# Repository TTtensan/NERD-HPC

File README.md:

# [NERD-HPC](https://github.com/TTtensan/NERD-HPC)

## アップデート方法
1. 本体とPCをUSBで接続する。
2. BOOTを押しながらPowerをONにする。もしくはPowerをONにした後にBOOTを押しながらRESETボタンを押す。
3. パソコンにRPI-RP2として認識されるのでsoftware/build/src/NERD_HPC.uf2をドラッグ&ドロップする。

## ファームウェアのビルド方法
どちらの方法でも、ビルド成果物は`software/build/src/NERD_HPC.uf2`に出力されます。

### コマンドラインでビルドする場合
```
(Ubuntu Desktop 24.04.1 LTS)
sudo apt install cmake python3 build-essential gcc-arm-none-eabi libnewlib-arm-none-eabi libstdc++-arm-none-eabi-newlib
```
```
git clone --recursive https://github.com/TTtensan/NERD-HPC.git
cd NERD-HPC/software
cmake -B build
cd build
make
```
この方法では、リポジトリに同梱されている`software/libraries/pico-sdk`(サブモジュール)を使ってビルドします。`--recursive`を忘れずに。

### VS Codeでビルドする場合
[Raspberry Pi Pico拡張機能](https://marketplace.visualstudio.com/items?itemName=raspberry-pi.raspberry-pi-pico)を使います。

1. リポジトリをクローンし、`software`フォルダをVS Codeで開く。
2. 推奨拡張機能のインストールを促されるので、インストールする(`.vscode/extensions.json`に定義しています)。
3. Pico拡張機能が必要なツールチェーンを`~/.pico-sdk`以下に自動でダウンロードします。使用するバージョンは`software/CMakeLists.txt`の先頭で指定しています(Pico SDK 2.2.0 / GCC 14_2_Rel1 / picotool 2.2.0-a4)。
4. サイドバーのPicoアイコンから`Compile Project`を実行する。

`.vscode`以下の設定はリポジトリで共有しています。パスはすべて`${userHome}`などの変数で書いてあるため、Windows・macOS・Linuxのいずれでもそのまま動作します。

なお、この方法ではコマンドラインの場合と違い、同梱のサブモジュールではなく`~/.pico-sdk`にダウンロードされたSDKが使われます。

## その他リンク
- 本家豊四季タイニーBASIC(Arduino版)。素晴らしいプログラムをオープンソースライセンスで公開いただいていること、大変感謝しています。製作者様に本オープンソースプロジェクトについて連絡済みです。GPLのバージョンはGPLv3とのこと。<br>[ttbasic\_arduino](https://github.com/vintagechips/ttbasic_arduino)

- CHR、2進数、16進数の処理はこちらを参考にしました。大変参考になりました。<br>[ttbasic\_arduino\_stm32](https://github.com/Tamakichi/ttbasic_arduino_stm32)

- フォントデータ。こちらをベースに一部変更しています。これによって少ないデータでフォントデータを実装することができました。ありがとうございます。<br>[ＡＱＭ１２４８Ａ グラフィックＬＣＤ (for Arduino)](https://hatakekara.com/aqm1248a/)

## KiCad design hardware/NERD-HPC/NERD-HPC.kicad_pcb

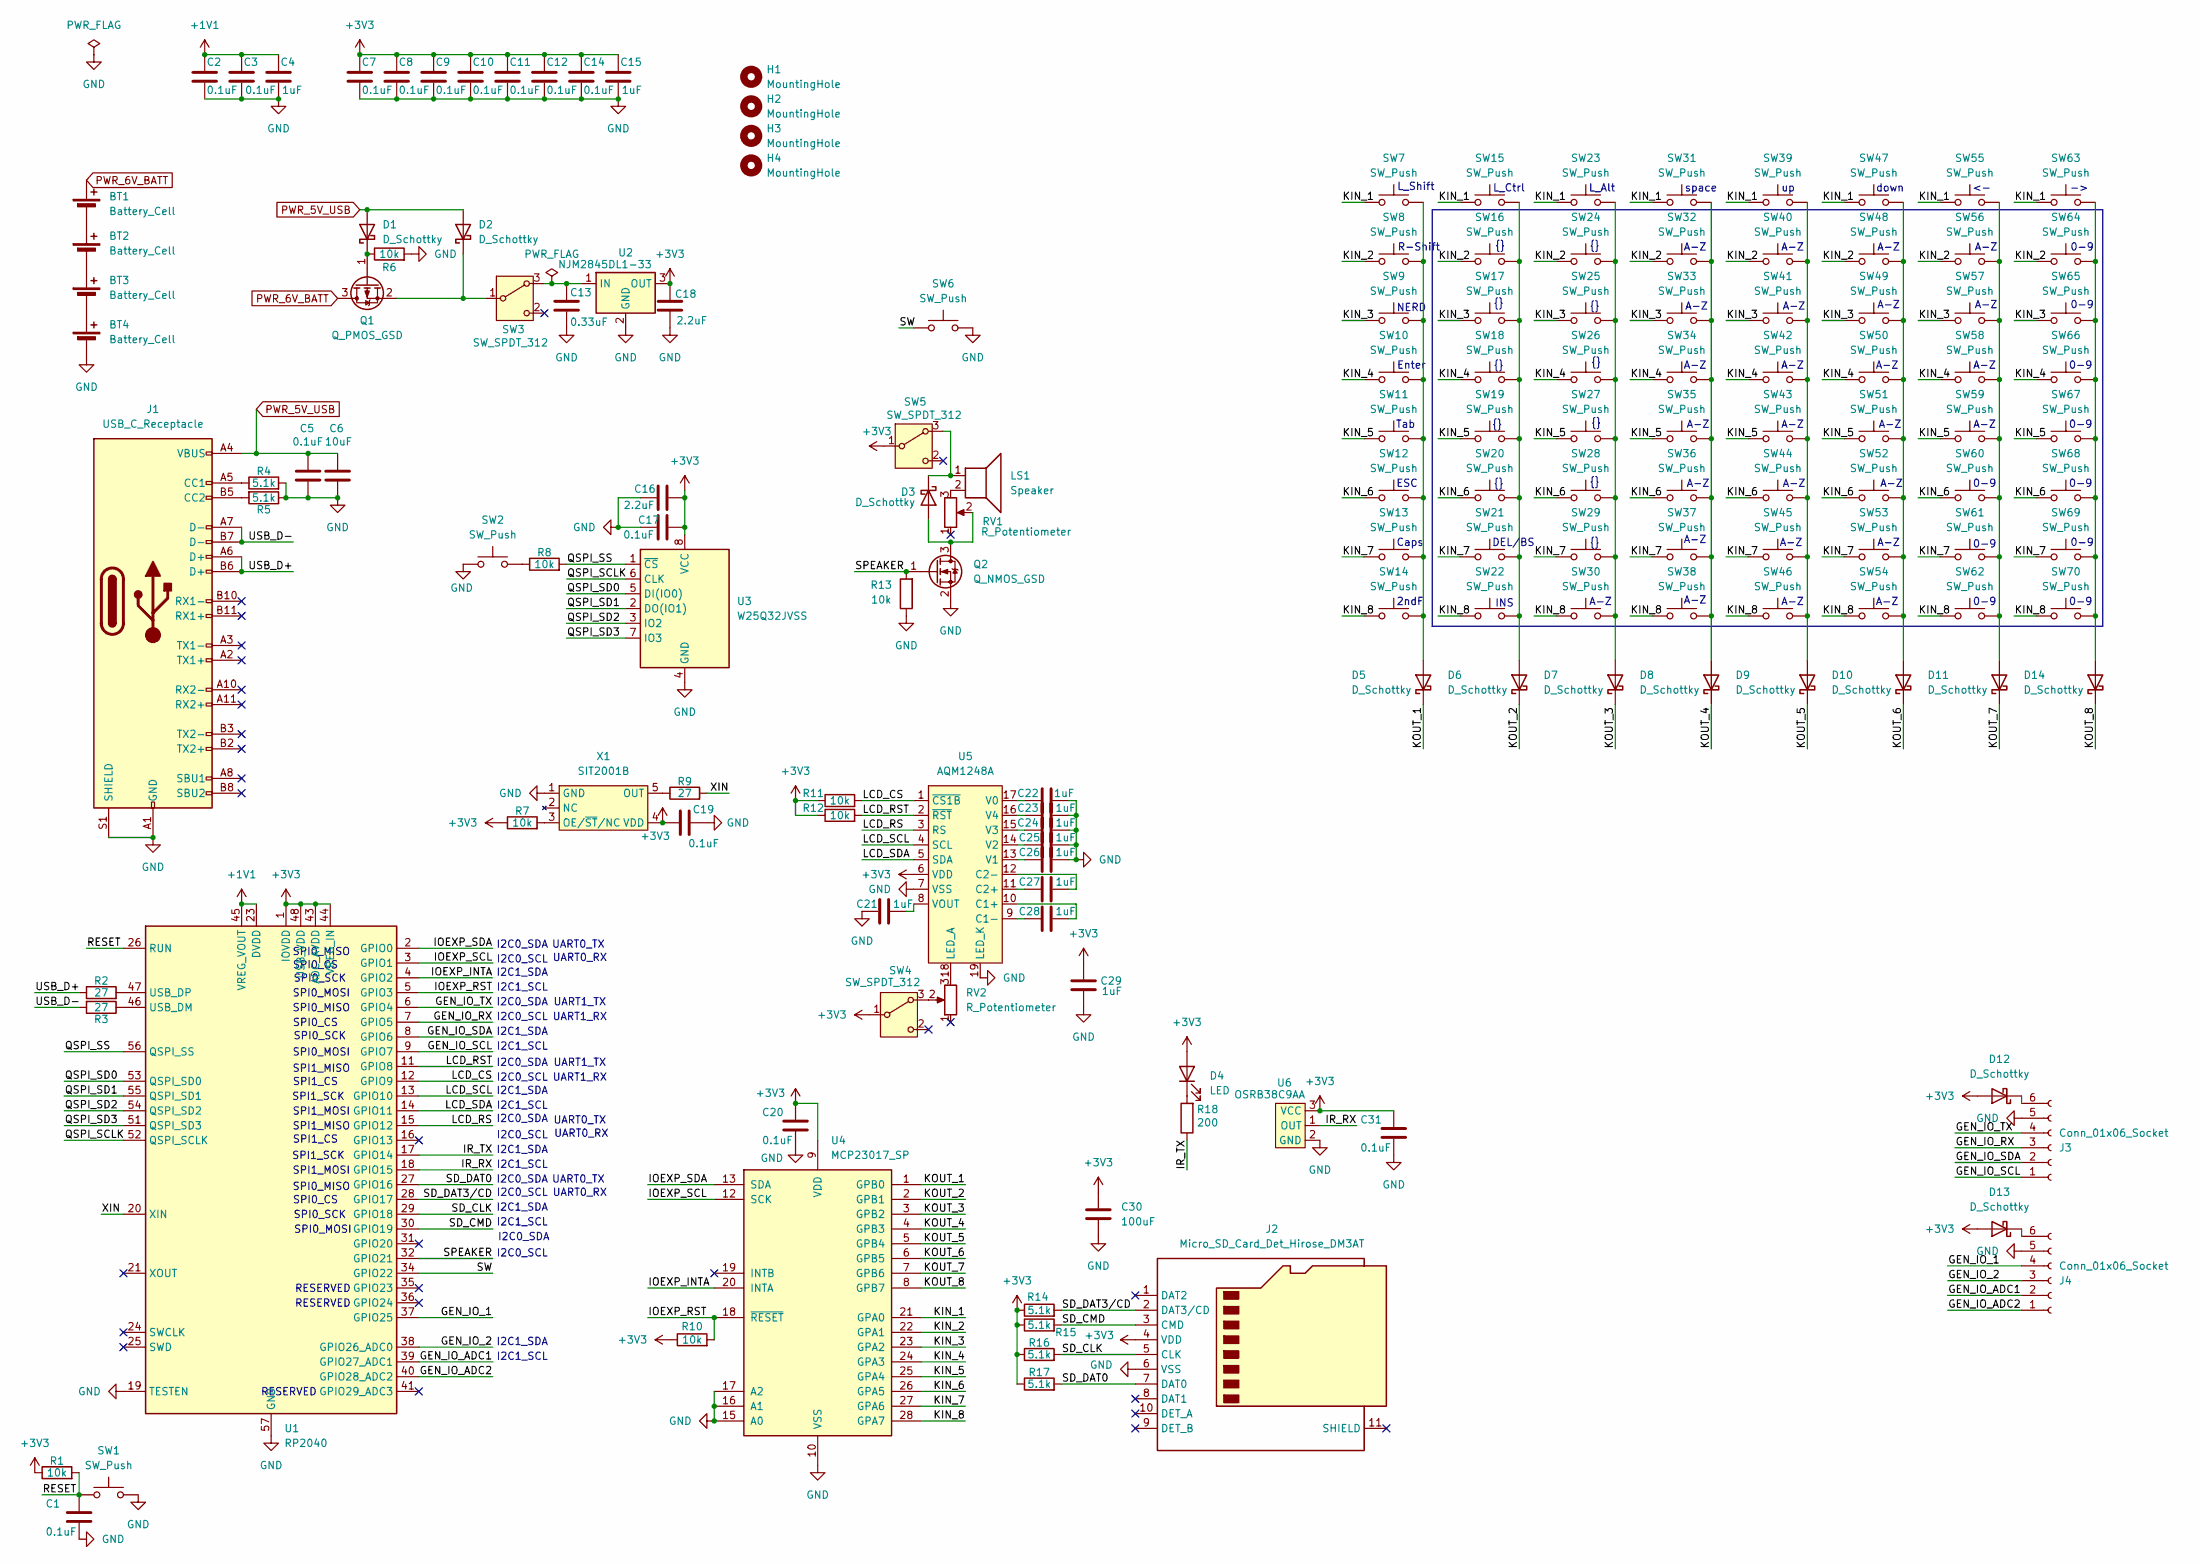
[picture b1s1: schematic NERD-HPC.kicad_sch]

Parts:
BT1, BT2, BT3, BT4: Battery_Cell; BatteryHolder_Keystone_2466_1xAAA
C1, C2, C3, C5, C7, C8, C9, C10, C11, C12, C14, C17, C19, C20, C31: 0.1uF; C_0603_1608Metric
C4, C15, C21, C22, C23, C24, C25, C26, C27, C28, C29: 1uF; C_0603_1608Metric
C6: 10uF; C_0603_1608Metric
C13: 0.33uF; C_0603_1608Metric
C16, C18: 2.2uF; C_0603_1608Metric
C30: 100uF; C_1206_3216Metric
D1, D2, D3, D5, D6, D7, D8, D9, D10, D11, D12, D13, D14: D_Schottky; CUS01
D4: LED; LED_D3.0mm
H1, H2, H3, H4: MountingHole; MountingHole_3.2mm_M3
J1: USB_C_Receptacle; USB_C_Receptacle_XKB_U262-16XN-4BVC11
J2: Micro_SD_Card_Det_Hirose_DM3AT; microSD_HC_Hirose_DM3AT-SF-PEJM5
J3, J4: Conn_01x06_Socket; PinSocket_1x06_P2.54mm_Vertical
LS1: Speaker; UM1515IA085008
Q1: Q_PMOS_GSD; SOT-23
Q2: Q_NMOS_GSD; SOT-23
R1, R6, R7, R8, R10, R11, R12, R13: 10k; R_0603_1608Metric
R2, R3, R9: 27; R_0603_1608Metric
R4, R5, R14, R15, R16, R17: 5.1k; R_0603_1608Metric
R18: 200; R_0603_1608Metric
RV1, RV2: R_Potentiometer; 3386K-EY5-101TR
SW1, SW2, SW6, SW7, SW8, SW9, SW10, SW11, SW12, SW13, SW14, SW15, SW16, SW17, SW18, SW19, SW20, SW21, SW22, SW23, SW24, SW25, SW26, SW27, SW28, SW29, SW30, SW31, SW32, SW33, SW34, SW35, SW36, SW37, SW38, SW39, SW40, SW41, SW42, SW43, SW44, SW45, SW46, SW47, SW48, SW49, SW50, SW51, SW52, SW53, SW54, SW55, SW56, SW57, SW58, SW59, SW60, SW61, SW62, SW63, SW64, SW65, SW66, SW67, SW68, SW69, SW70: SW_Push; SW_PUSH_6mm
SW3, SW4, SW5: SW_SPDT_312; SS-12D00-G5
U1: RP2040; QFN-56-1EP_7x7mm_P0.4mm_EP3.2x3.2mm
U2: NJM2845DL1-33; TO-252-3_TabPin2
U3: W25Q32JVSS; Winbond_USON-8-1EP_3x2mm_P0.5mm_EP0.2x1.6mm
U4: MCP23017_SP; DIP-28_W7.62mm
U5: AQM1248A
U6: OSRB38C9AA
X1: SIT2001B; SOT-23-5

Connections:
+1V1: C2.1, C3.1, C4.1, U1.23 (DVDD), U1.45 (VREG_VOUT), U1.50 (DVDD)
+3V3: C7.1, C8.1, C9.1, C10.1, C11.1, C12.1, C14.1, C15.1, C16.2, C17.1, C18.1, C19.2, C20.1, C29.1, C30.1, C31.1, D4.2 (A), D12.2 (A), D13.2 (A), J2.4 (VDD), R1.1, R7.1, R10.1, R11.1, R12.1, R14.1, R15.1, R16.1, R17.1, SW4.1 (B), SW5.1 (B), U1.1 (IOVDD), U1.10 (IOVDD), U1.22 (IOVDD), U1.33 (IOVDD), U1.42 (IOVDD), U1.43 (ADC_AVDD), U1.44 (VREG_IN), U1.48 (USB_VDD), U1.49 (IOVDD), U2.3 (OUT), U3.8 (VCC), U4.9 (VDD), U5.6 (VDD), U6.3 (VCC), X1.4 (VDD)
/GEN_IO_1: J4.4, U1.37 (GPIO25)
/GEN_IO_2: J4.3, U1.38 (GPIO26_ADC0)
/GEN_IO_ADC1: J4.2, U1.39 (GPIO27_ADC1)
/GEN_IO_ADC2: J4.1, U1.40 (GPIO28_ADC2)
/GEN_IO_RX: J3.3, U1.7 (GPIO5)
/GEN_IO_SCL: J3.1, U1.9 (GPIO7)
/GEN_IO_SDA: J3.2, U1.8 (GPIO6)
/GEN_IO_TX: J3.4, U1.6 (GPIO4)
/IOEXP_INTA: U1.4 (GPIO2), U4.20 (INTA)
/IOEXP_RST: R10.2, U1.5 (GPIO3), U4.18 (~RESET)
/IOEXP_SCL: U1.3 (GPIO1), U4.12 (SCK)
/IOEXP_SDA: U1.2 (GPIO0), U4.13 (SDA)
/IR_RX: U1.18 (GPIO15), U6.1 (OUT)
/IR_TX: R18.1, U1.17 (GPIO14)
/KIN_1: SW7.1, SW15.1, SW23.1, SW31.1, SW39.1, SW47.1, SW55.1, SW63.1, U4.21 (GPA0)
/KIN_2: SW8.1, SW16.1, SW24.1, SW32.1, SW40.1, SW48.1, SW56.1, SW64.1, U4.22 (GPA1)
/KIN_3: SW9.1, SW17.1, SW25.1, SW33.1, SW41.1, SW49.1, SW57.1, SW65.1, U4.23 (GPA2)
/KIN_4: SW10.1, SW18.1, SW26.1, SW34.1, SW42.1, SW50.1, SW58.1, SW66.1, U4.24 (GPA3)
/KIN_5: SW11.1, SW19.1, SW27.1, SW35.1, SW43.1, SW51.1, SW59.1, SW67.1, U4.25 (GPA4)
/KIN_6: SW12.1, SW20.1, SW28.1, SW36.1, SW44.1, SW52.1, SW60.1, SW68.1, U4.26 (GPA5)
/KIN_7: SW13.1, SW21.1, SW29.1, SW37.1, SW45.1, SW53.1, SW61.1, SW69.1, U4.27 (GPA6)
/KIN_8: SW14.1, SW22.1, SW30.1, SW38.1, SW46.1, SW54.1, SW62.1, SW70.1, U4.28 (GPA7)
/KOUT_1: D5.1 (K), U4.1 (GPB0)
/KOUT_2: D6.1 (K), U4.2 (GPB1)
/KOUT_3: D7.1 (K), U4.3 (GPB2)
/KOUT_4: D8.1 (K), U4.4 (GPB3)
/KOUT_5: D9.1 (K), U4.5 (GPB4)
/KOUT_6: D10.1 (K), U4.6 (GPB5)
/KOUT_7: D11.1 (K), U4.7 (GPB6)
/KOUT_8: D14.1 (K), U4.8 (GPB7)
/LCD_CS: R11.2, U1.12 (GPIO9), U5.1 (~CS1B)
/LCD_RS: U1.15 (GPIO12), U5.3 (RS)
/LCD_RST: R12.2, U1.11 (GPIO8), U5.2 (~RST)
/LCD_SCL: U1.13 (GPIO10), U5.4 (SCL)
/LCD_SDA: U1.14 (GPIO11), U5.5 (SDA)
/QSPI_SCLK: U1.52 (QSPI_SCLK), U3.6 (CLK)
/QSPI_SD0: U1.53 (QSPI_SD0), U3.5 (DI(IO0))
/QSPI_SD1: U1.55 (QSPI_SD1), U3.2 (DO(IO1))
/QSPI_SD2: U1.54 (QSPI_SD2), U3.3 (IO2)
/QSPI_SD3: U1.51 (QSPI_SD3), U3.7 (IO3)
/QSPI_SS: R8.2, U1.56 (QSPI_SS), U3.1 (~CS)
/RESET: C1.1, R1.2, SW1.1, U1.26 (RUN)
/SD_CLK: J2.5 (CLK), R16.2, U1.29 (GPIO18)
/SD_CMD: J2.3 (CMD), R15.2, U1.30 (GPIO19)
/SD_DAT0: J2.7 (DAT0), R17.2, U1.27 (GPIO16)
/SD_DAT3/CD: J2.2 (DAT3/CD), R14.2, U1.28 (GPIO17)
/SPEAKER: Q2.1 (G), R13.2, U1.32 (GPIO21)
/SW: SW6.1, U1.34 (GPIO22)
/USB_D+: J1.A6 (D+), J1.B6 (D+), R2.1
/USB_D-: J1.A7 (D-), J1.B7 (D-), R3.2
/XIN: R9.2, U1.20 (XIN)
GND: BT4.2 (-), C1.2, C2.2, C3.2, C4.2, C5.2, C6.2, C7.2, C8.2, C9.2, C10.2, C11.2, C12.2, C13.2, C14.2, C15.2, C16.1, C17.2, C18.2, C19.1, C20.2, C21.1, C22.2, C23.2, C24.2, C25.2, C26.2, C29.2, C30.2, C31.2, J1.A1 (GND), J1.A12 (GND), J1.B1 (GND), J1.B12 (GND), J1.S1 (SHIELD), J2.6 (VSS), J3.5, J4.5, Q2.2 (S), R4.2, R5.1, R6.2, R13.1, SW1.2, SW2.1, SW6.2, U1.19 (TESTEN), U1.57 (GND), U2.2 (GND), U3.4 (GND), U4.10 (VSS), U4.15 (A0), U4.16 (A1), U4.17 (A2), U5.7 (VSS), U5.19 (LED_K), U6.2 (GND), X1.1 (GND)
unnamed: BT1.2 (-), BT2.1 (+)
unnamed: BT2.2 (-), BT3.1 (+)
unnamed: BT3.2 (-), BT4.1 (+)
unnamed: D1.1 (K), Q1.1 (G), R6.1
unnamed: D2.1 (K), Q1.2 (S), SW3.1 (B)
unnamed: D3.2 (A), Q2.3 (D), RV1.2
unnamed: D3.1 (K), LS1.1, SW5.3 (A)
unnamed: D4.1 (K), R18.2
unnamed: D5.2 (A), SW7.2, SW8.2, SW9.2, SW10.2, SW11.2, SW12.2, SW13.2, SW14.2
unnamed: D6.2 (A), SW15.2, SW16.2, SW17.2, SW18.2, SW19.2, SW20.2, SW21.2, SW22.2
unnamed: D7.2 (A), SW23.2, SW24.2, SW25.2, SW26.2, SW27.2, SW28.2, SW29.2, SW30.2
unnamed: D8.2 (A), SW31.2, SW32.2, SW33.2, SW34.2, SW35.2, SW36.2, SW37.2, SW38.2
unnamed: D9.2 (A), SW39.2, SW40.2, SW41.2, SW42.2, SW43.2, SW44.2, SW45.2, SW46.2
unnamed: D10.2 (A), SW47.2, SW48.2, SW49.2, SW50.2, SW51.2, SW52.2, SW53.2, SW54.2
unnamed: D11.2 (A), SW55.2, SW56.2, SW57.2, SW58.2, SW59.2, SW60.2, SW61.2, SW62.2
unnamed: D12.1 (K), J3.6
unnamed: D13.1 (K), J4.6
unnamed: D14.2 (A), SW63.2, SW64.2, SW65.2, SW66.2, SW67.2, SW68.2, SW69.2, SW70.2
unnamed: J1.A5 (CC1), R4.1
unnamed: J1.B5 (CC2), R5.2
unnamed: LS1.2, RV1.3
unnamed: R8.1, SW2.2
unnamed: C13.1, SW3.3 (A), U2.1 (IN)
unnamed: RV2.2, SW4.3 (A)
unnamed: R3.1, U1.46 (USB_DM)
unnamed: R2.2, U1.47 (USB_DP)
unnamed: C28.2, U5.10 (C1+)
unnamed: C28.1, U5.9 (C1-)
unnamed: C27.1, U5.11 (C2+)
unnamed: C27.2, U5.12 (C2-)
unnamed: RV2.3, U5.18 (LED_A)
unnamed: C22.1, U5.17 (V0)
unnamed: C26.1, U5.13 (V1)
unnamed: C25.1, U5.14 (V2)
unnamed: C24.1, U5.15 (V3)
unnamed: C23.1, U5.16 (V4)
unnamed: C21.2, U5.8 (VOUT)
unnamed: R7.2, X1.3 (OE/~ST/NC)
unnamed: R9.1, X1.5 (OUT)
PWR_5V_USB: C5.1, C6.1, D1.2 (A), D2.2 (A), J1.A4 (VBUS), J1.A9 (VBUS), J1.B4 (VBUS), J1.B9 (VBUS)
PWR_6V_BATT: BT1.1 (+), Q1.3 (D)

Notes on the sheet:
A-Z
I2C1_SDA
I2C0_SDA
ESC
SPI1_MOSI
0-9
UART0_RX
2ndF
Tab
SPI0_SCK
I2C1_SCL
I2C0_SCL
RESERVED
DEL/BS
SPI0_CS
Caps
SPI0_MISO
SPI1_CS
UART1_RX
Enter
SPI1_SCK
R-Shift
down
UART1_TX
SPI0_MOSI
SPI1_MISO
L_Ctrl
UART0_TX
NERD
L_Alt
L_Shift
INS
space

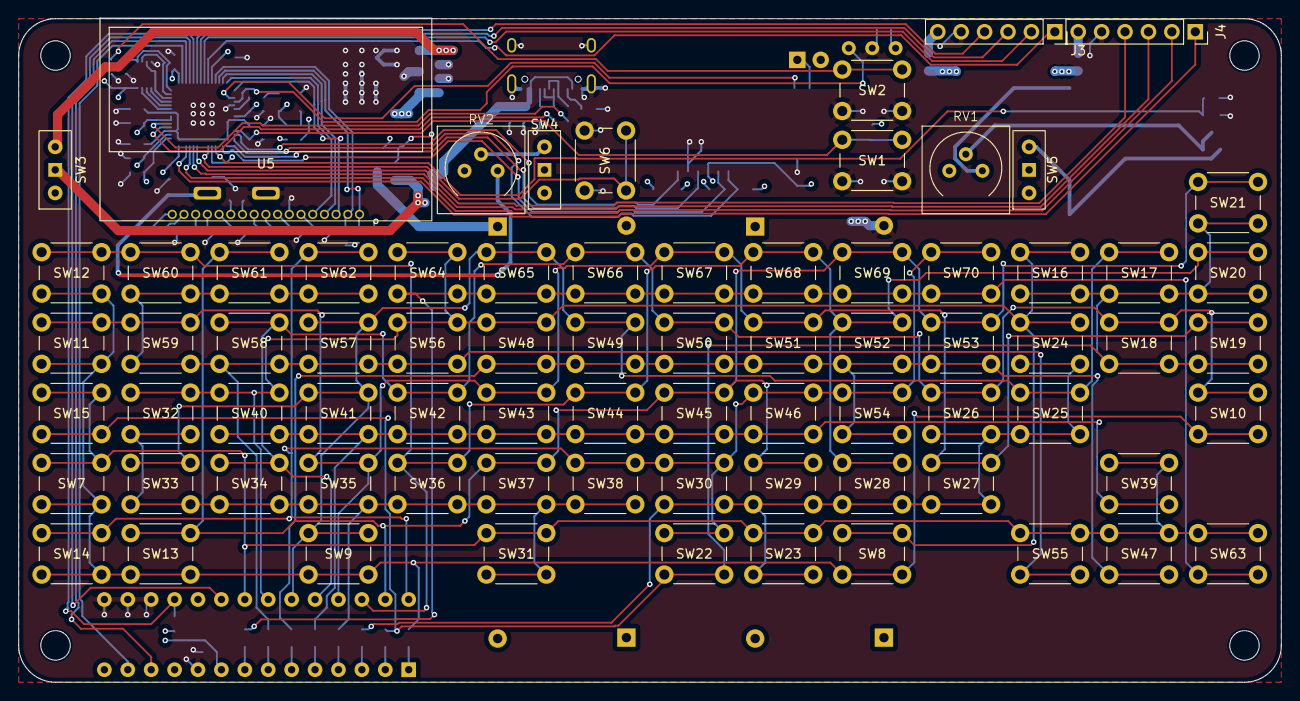
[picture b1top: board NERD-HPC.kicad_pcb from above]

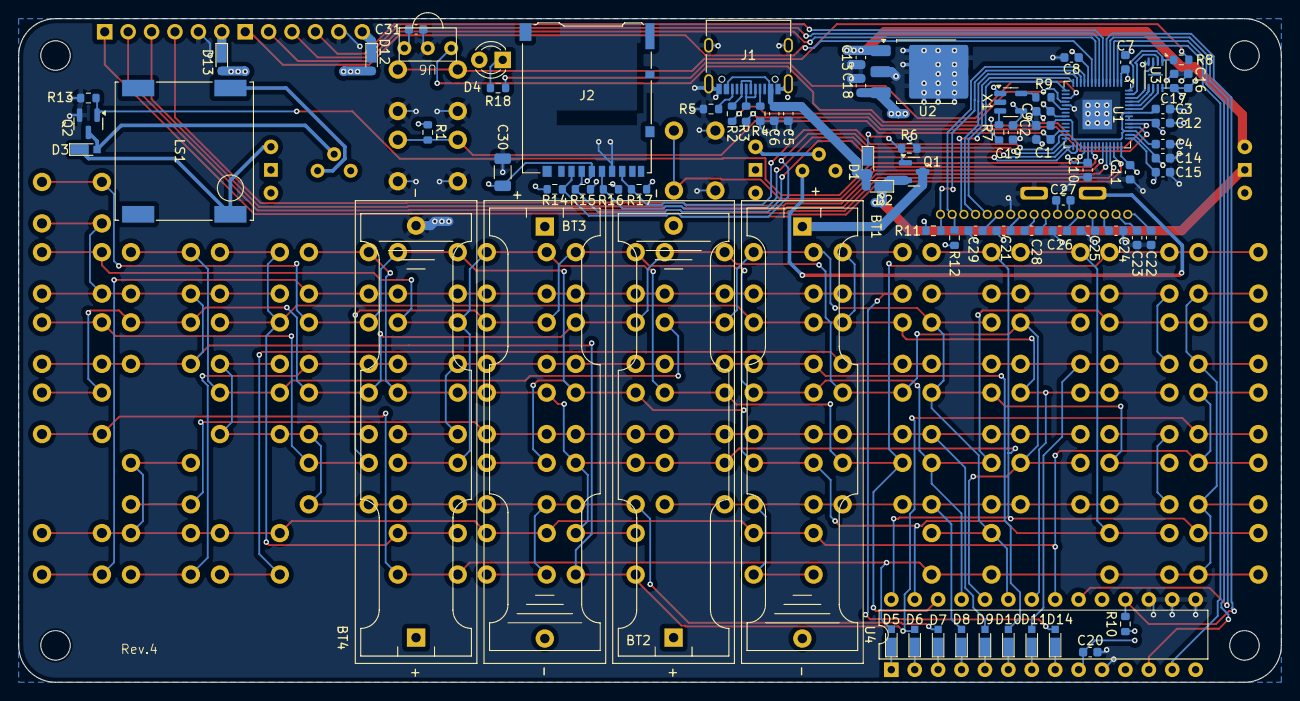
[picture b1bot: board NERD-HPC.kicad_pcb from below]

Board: 4 copper layers, 137.0 x 72.0 mm, 157 parts (78 on the bottom side), 95 nets.

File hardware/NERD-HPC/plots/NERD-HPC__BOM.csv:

Reference,Value,Datasheet,Footprint,Qty,DNP
"BT1,BT2,BT3,BT4",Battery_Cell,https://akizukidenshi.com/catalog/g/g102670/,Battery:BatteryHolder_Keystone_2466_1xAAA,4,
"C1,C2,C3,C5,C7,C8,C9,C10,C11,C12,C14,C17,C19,C20,C31",0.1uF,https://akizukidenshi.com/catalog/g/g113374/,Capacitor_SMD:C_0603_1608Metric,15,
"C4,C15,C21,C22,C23,C24,C25,C26,C27,C28,C29",1uF,https://akizukidenshi.com/catalog/g/g114526/,Capacitor_SMD:C_0603_1608Metric,11,
C6,10uF,https://akizukidenshi.com/catalog/g/g113161/,Capacitor_SMD:C_0603_1608Metric,1,
C13,0.47uF,https://akizukidenshi.com/catalog/g/g114554/,Capacitor_SMD:C_0603_1608Metric,1,
"C16,C18",2.2uF,https://akizukidenshi.com/catalog/g/g116077/,Capacitor_SMD:C_0603_1608Metric,2,
C30,100uF,https://akizukidenshi.com/catalog/g/g115633/,Capacitor_SMD:C_1206_3216Metric,1,
"D1,D2,D3,D5,D6,D7,D8,D9,D10,D11,D12,D13,D14",D_Schottky,https://akizukidenshi.com/catalog/g/g111231/,LocalFootprintLibrary:CUS01,13,
D4,LED,https://akizukidenshi.com/catalog/g/g104313/,LED_THT:LED_D3.0mm,1,
J1,USB_C_Receptacle,https://akizukidenshi.com/catalog/g/g114356/,Connector_USB:USB_C_Receptacle_XKB_U262-16XN-4BVC11,1,
J2,Micro_SD_Card_Det_Hirose_DM3AT,https://akizukidenshi.com/catalog/g/g102395/,Connector_Card:microSD_HC_Hirose_DM3AT-SF-PEJM5,1,
"J3,J4",Conn_01x06_Socket,https://akizukidenshi.com/catalog/g/g103784/,Connector_PinSocket_2.54mm:PinSocket_1x06_P2.54mm_Vertical,2,
LS1,Speaker,https://akizukidenshi.com/catalog/g/g106707/,LocalFootprintLibrary:UM1515IA085008,1,
Q1,Q_PMOS_GSD,https://akizukidenshi.com/catalog/g/g102553/,Package_TO_SOT_SMD:SOT-23,1,
Q2,Q_NMOS_GSD,https://akizukidenshi.com/catalog/g/g106049/,Package_TO_SOT_SMD:SOT-23,1,
"R1,R6,R7,R8,R10,R11,R12,R13",10k,https://akizukidenshi.com/catalog/g/g115029/,Resistor_SMD:R_0603_1608Metric,8,
"R2,R3,R9",27,free,Resistor_SMD:R_0603_1608Metric,3,
"R4,R5,R14,R15,R16,R17",5.1k,https://www.sengoku.co.jp/mod/sgk_cart/detail.php?code=EEHD-57GS,Resistor_SMD:R_0603_1608Metric,6,
R18,200,free,Resistor_SMD:R_0603_1608Metric,1,
"RV1,RV2",R_Potentiometer,https://akizukidenshi.com/catalog/g/g106099/,LocalFootprintLibrary:3386K-EY5-101TR,2,
"SW1,SW2,SW6,SW7,SW8,SW9,SW10,SW11,SW12,SW13,SW14,SW15,SW16,SW17,SW18,SW19,SW20,SW21,SW22,SW23,SW24,SW25,SW26,SW27,SW28,SW29,SW30,SW31,SW32,SW33,SW34,SW35,SW36,SW37,SW38,SW39,SW40,SW41,SW42,SW43,SW44,SW45,SW46,SW47,SW48,SW49,SW50,SW51,SW52,SW53,SW54,SW55,SW56,SW57,SW58,SW59,SW60,SW61,SW62,SW63,SW64,SW65,SW66,SW67,SW68,SW69,SW70",SW_Push,https://akizukidenshi.com/catalog/g/g103648/,Button_Switch_THT:SW_PUSH_6mm,67,
"SW3,SW4,SW5",SW_SPDT_312,https://akizukidenshi.com/catalog/g/g112723/,LocalFootprintLibrary:SS-12D00-G5,3,
U1,RP2040,https://akizukidenshi.com/catalog/g/g117056/,Package_DFN_QFN:QFN-56-1EP_7x7mm_P0.4mm_EP3.2x3.2mm,1,
U2,NJM2845DL1-33,https://akizukidenshi.com/catalog/g/g111299/,Package_TO_SOT_SMD:TO-252-3_TabPin2,1,
U3,W25Q32JVSS,https://akizukidenshi.com/catalog/g/g117346/,Package_SON:Winbond_USON-8-1EP_3x2mm_P0.5mm_EP0.2x1.6mm,1,
U4,MCP23017_SP,https://akizukidenshi.com/catalog/g/g109486/,Package_DIP:DIP-28_W7.62mm,1,
U5,AQM1248A,https://akizukidenshi.com/catalog/g/g110048/,LocalFootprintLibrary:AQM1248A,1,
U6,OSRB38C9AA,https://akizukidenshi.com/catalog/g/g104659/,LocalFootprintLibrary:OSRB38C9AA,1,
X1,SIT2001B,https://akizukidenshi.com/catalog/g/g111093/,Package_TO_SOT_SMD:SOT-23-5,1,

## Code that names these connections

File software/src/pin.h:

#ifndef PIN_H_
#define PIN_H_

#include "hardware/i2c.h"

#define PIN_IOEXP_SDA 0
#define PIN_IOEXP_SCL 1
#define PIN_IOEXP_INTA 2
#define PIN_IOEXP_RST 3

#define PIN_GEN_IO_TX 4
#define PIN_GEN_IO_RX 5
#define PIN_GEN_IO_SDA 6
#define PIN_GEN_IO_SCL 7

#define PIN_LCD_RST 8
#define PIN_LCD_CS 9
#define PIN_LCD_SCL 10
#define PIN_LCD_SDA 11
#define PIN_LCD_RS 12

#define PIN_IR_TX 14
#define PIN_IR_RX 15

#define PIN_SD_DAT0 16
#define PIN_SD_DAT3 17
#define PIN_SD_CLK 18
#define PIN_SD_CMD 19

#define PIN_SPEAKER 21
#define PIN_SW 22

#define PIN_GEN_IO_1 25
#define PIN_GEN_IO_2 26
#define PIN_GEN_IO_3 27
#define PIN_GEN_IO_4 28

#define UART_ID_GENIO uart1
#define I2C_ID_GENIO i2c1

// 1MHz(Fast-mode Plus)は外付けプルアップが1kΩ級でないと成立しない。
// 1MHzではIOピンに指で触れただけでバスが完全無応答になり、
// MCP23017のレジスタが化けたり、キー入力が2秒ほど止まったりしていた。
// 400kHzに落とすと再現しなくなったので、こちらを採用する。
// プルアップ抵抗を1kΩ級に見直せば1MHzへ戻せる
#define I2C0_BAUDRATE 400000

void pin_init();

#endif

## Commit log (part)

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2025-01-01 add hardware file
2025-01-01 update bom
2025-01-01 add firmware(tmp)
2025-01-01 add firmware
2025-01-01 add pico sdk
2025-01-01 rm submodule
2025-01-01 use libraries/pico-sdk
2025-01-02 add GLINE, GCIRCLE. assign arrow keycode.
2025-01-03 add PLYSND STPSND
2025-01-09 add GRECT
2025-01-11 add IOSD,IOPU,IOPD,IODP,IOPUT,IOGET
2025-01-13 include dev_hid_composite sample
2025-01-13 enable CDC
2025-01-13 fix endpoint num
2025-01-13 send b
2025-01-13 send c while 5 seconds
2025-01-13 add get and set hid keycode function
2025-01-13 handle keyboard task in core1
2025-01-13 access current_keycode
2025-01-13 add SNDKCD
2025-01-13 send multiple keycode
2025-01-14 fix keycode and increase list size
2025-01-14 add en_shift, en_esc flg
2025-01-14 add keycode and fix keycode
2025-01-14 add shift code
2025-01-14 v1.5.0
2025-01-16 add program storage area
2025-01-18 initial reset lcd and ioexpander
2025-01-18 v1.5.2
2025-01-18 NERD HPC pcb Rev.4
2025-01-18 NERD HPC CASE F pcb Rev.4
2025-01-18 add assembly pdf
2025-01-18 add BOM file
2025-01-18 move plot file
2025-01-23 change pico sdk v1.4.0 to v2.1.0
2025-01-23 build with pico-sdk v2.1.0
2025-01-23 fix problem
2025-01-23 v1.5.3
2025-01-25 update LIST instruction
2025-01-25 v1.6.0
2025-01-26 overwrite save
2025-01-26 v1.6.1
2025-01-26 do not show the list when no program is entered
2025-01-26 v1.6.2
2025-02-04 add MSC
2025-02-04 change Volume name
2025-02-04 add msc description
2025-02-11 v1.5.3d
2025-02-11 add GEN IO uart
2025-06-04 add i2c function
2025-06-05 change IOUG to IOUS
2025-06-05 v1.7.0
2025-06-12 tmp version v1.7.1d
2025-06-16 fix GCLS cursor position and IOUR IOIR
2025-06-16 v1.7.1
2025-06-26 add font data and init font
2025-07-02 add kana font
2025-07-07 add GPUTC
2025-07-07 add reference font data URL
2025-07-08 update stack size
2025-07-08 add modulo operation
2025-07-08 fixed conflict
2025-07-08 update version
2025-07-13 change to develop version
2025-07-13 add IRPUT IRGET
2025-07-14 add SETF RESETF
2025-07-14 Revert "Feature edit font"
2025-07-14 rebuild
2025-07-17 start v1.9.0d
2025-07-21 add DELETE
2025-07-21 expand array
2025-07-22 add CHR
2025-07-22 add LOCATE
2025-07-22 execute AUTORUN.TXT
2025-07-22 v1.10.0
2025-07-25 start v1.10.0d and add bit operation
2025-07-26 add SCR
2025-07-26 fix hex bin display and save
2025-07-26 fix README
2025-07-26 change version to v1.11.0
2025-08-30 fix fill bug
2025-08-30 change version name v1.11.1
2025-09-04 update spec
2025-09-05 add GPGET
2025-09-05 add GTRI
2025-09-14 RUN filename
2025-09-22 change timer irq to pin irq
2025-09-23 use ring buffer
2025-09-23 update prev_keyinfo
2025-09-26 change to timer interrupt and add i2c recovery process
2025-09-27 v1.13.0
2025-10-02 disable i2c recovery process
2025-10-02 v1.13.1 beta1
2025-10-08 v1.13.1
2025-10-08 rebase develop-software
2025-10-08 add bin file
2025-10-09 code refactoring
2025-10-09 add screen argument to draw function
2025-10-09 display cursor
2025-10-09 hide cursor while running program
2025-10-09 left cursor move
2025-10-09 right cursor move
2026-04-29 tmp commit
2026-04-29 clear src buff only when cls
2026-05-19 Update README to include project link
2026-05-19 register google search
2026-05-19 v1.13.2
